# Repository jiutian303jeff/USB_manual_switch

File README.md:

# USB-A Physical Isolation Switch
---

## 📢 Current Update 
## (August 30, 2026)
### Overview & current update link: https://docs.google.com/document/d/1pLDk2mAq172Uoo87mN2TMu-KEBSsqmwrNO6xUET-iXo/edit?usp=drive_link

**Ver 2.0 Final Fabrication Release & Design Freeze**
* **TVS ESD Protection Integration**: Integrated an industrial-grade **SRV05-4** TVS diode array to clamp electrostatic discharge and voltage spikes during hot-plugging.
* ** D+/D-  Signal Tuning**: Executed single-track serpentine length tuning on differential signal traces to optimize USB 2.0 signal integrity.
* **100% Single-Sided Top Placement**: Re-engineered component placement, consolidating all connectors, switches, TVS ICs, and LEDs onto the Top Layer F.Cu for an improved visual aesthetic and lower-cost single-sided SMT reflow.
* **Ground Copper Pour**: Replaced thin discrete ground tracks with continuous Top and Bottom Ground Planes to minimize impedance and lower EMI.
* **Manufacturing Package**: All production Gerber files, drill files have been verified via KiCAD DRC (0 Errors) and packaged for fabrication.

---

##  Product Overview

The **USB-A Physical Isolation Switch** is an air-gapped hardware security and power management device designed in KiCAD 9.0. Unlike software-based toggles that rely on OS drivers and remain vulnerable to remote exploits, this hardware module provides a physical "hard-cut" for USB-connected peripherals. It ensures absolute data privacy, prevents unauthorized data exfiltration, and offers convenient hardware resetting without the mechanical wear of repeated plugging/unplugging.

note: content will change over time based on latest updates

---

##  Key Features

* **Air-Gapped Privacy & Security**: Physical DPDT switch physically breaks  V_{BUS}  power and  D+  data lines for 100% reliable hardware-level isolation.
* **Sub-Nanosecond ESD Protection**: Integrated **SRV05-4** TVS diode array clamps voltage transients across  V_{BUS} ,  D+ , and  D-  lines.
* **Matched Differential Pair ( 0.00\text{ mm}  Skew)**: Serpentine length tuning compensates for trace length differences caused by switch cutouts, maintaining data integrity.
* **Single-Sided SMT Layout**: Unified component layout on the top side simplifies assembly and provides a clean, professional finish.
* **Solid Grounding & EMI Reduction**: Continuous Ground Copper Pour (GND Zone) on both layers reduces ground loop impedance and improves heat dissipation.
* **Dual-LED Status Indication**:
  * 🟢 **Green LED ( ON\_GREEN )**: Active connection ( V_BUS  and data lines fully connected).
  * 🔴 **Red LED ( OFF\_RED )**: Isolated/OFF state ( V_BUS  disconnected from downstream port, routing through a  220,mega  resistor).

---

## 📁 File content

```text
.
├── final.zip                            # Complete manufacturing package (All Gerbers, Drill files etc)
├── USB-A switch overview.pdf            # Initial Ver 1.0 baseline documentation & overall project concept https://docs.google.com/document/d/1pLDk2mAq172Uoo87mN2TMu-KEBSsqmwrNO6xUET-iXo/edit?usp=drive_link
├── USB-A switch ver-xx.xx_update.pdf    # Updating report detailing new elements, technical iteration & design rationale https://docs.google.com/document/d/1X9TlPd9sVfkH2GCSMDSQgF4tiR_iDZ1_ytxDP3pgHG8/edit?usp=sharing
├── new_KiCAD_thing.kicad_pcb            # KiCAD PCB layout source file
├── new_KiCAD_thing.kicad_sch            # KiCAD schematic source file
├── PCB.png                              # High-resolution PCB Layout diagram preview
├── Schematic.png                        # High-resolution Schematic diagram preview
└── README.md                            # Project documentation
```

## 👤 Author & Acknowledgments

* **Author**: Haoyang Jiang
* **Date**: August 30, 2026
* **Designed With**: KiCAD EDA 9.0

---

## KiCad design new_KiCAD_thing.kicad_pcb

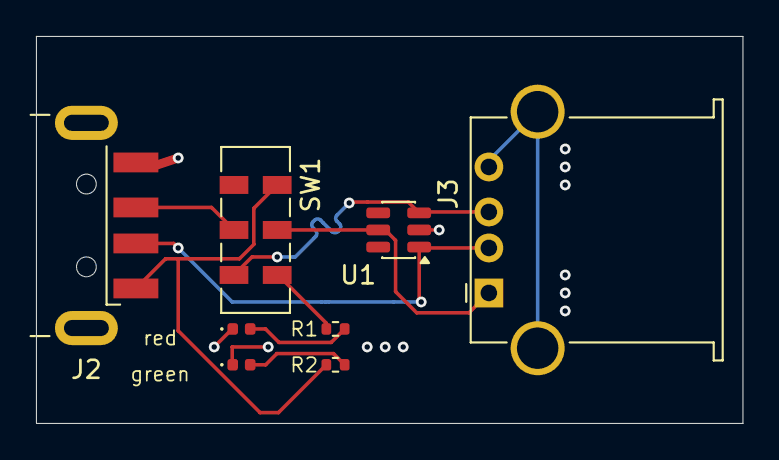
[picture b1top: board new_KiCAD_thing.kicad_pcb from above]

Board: 2 copper layers, 39.2 x 21.5 mm, 8 parts (0 on the bottom side), 9 nets.

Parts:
J2: USB_A_CNCTech_1001-011-01101_Horizontal
J3: USB_A; USB_A_Stewart_SS-52100-001_Horizontal
R1, R2: 220ohms; R_0402_1005Metric
SW1: SW_Slide_DPDT; SW_DPDT_CK_JS202011JCQN
U1: SRV05-4; SOT-23-6
green: LED; LED_0402_1005Metric
red: LED; LED_0402_1005Metric

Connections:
GNDREF: J2.4, J3.4 (GND), J3.5 (Shield), U1.2 (VN), green.1 (K), red.1 (K)
unnamed: J2.1, R2.1, SW1.1 (A)
unnamed: J2.3, SW1.5 (B)
unnamed: J3.3 (D+), SW1.6 (C), U1.3 (IO2)
unnamed: J2.2, J3.2 (D-), U1.1 (IO1)
unnamed: J3.1 (VBUS), SW1.2 (B), U1.5 (VP)
unnamed: R1.2, red.2 (A)
unnamed: R2.2, green.2 (A)
unnamed: R1.1, SW1.3 (C)
